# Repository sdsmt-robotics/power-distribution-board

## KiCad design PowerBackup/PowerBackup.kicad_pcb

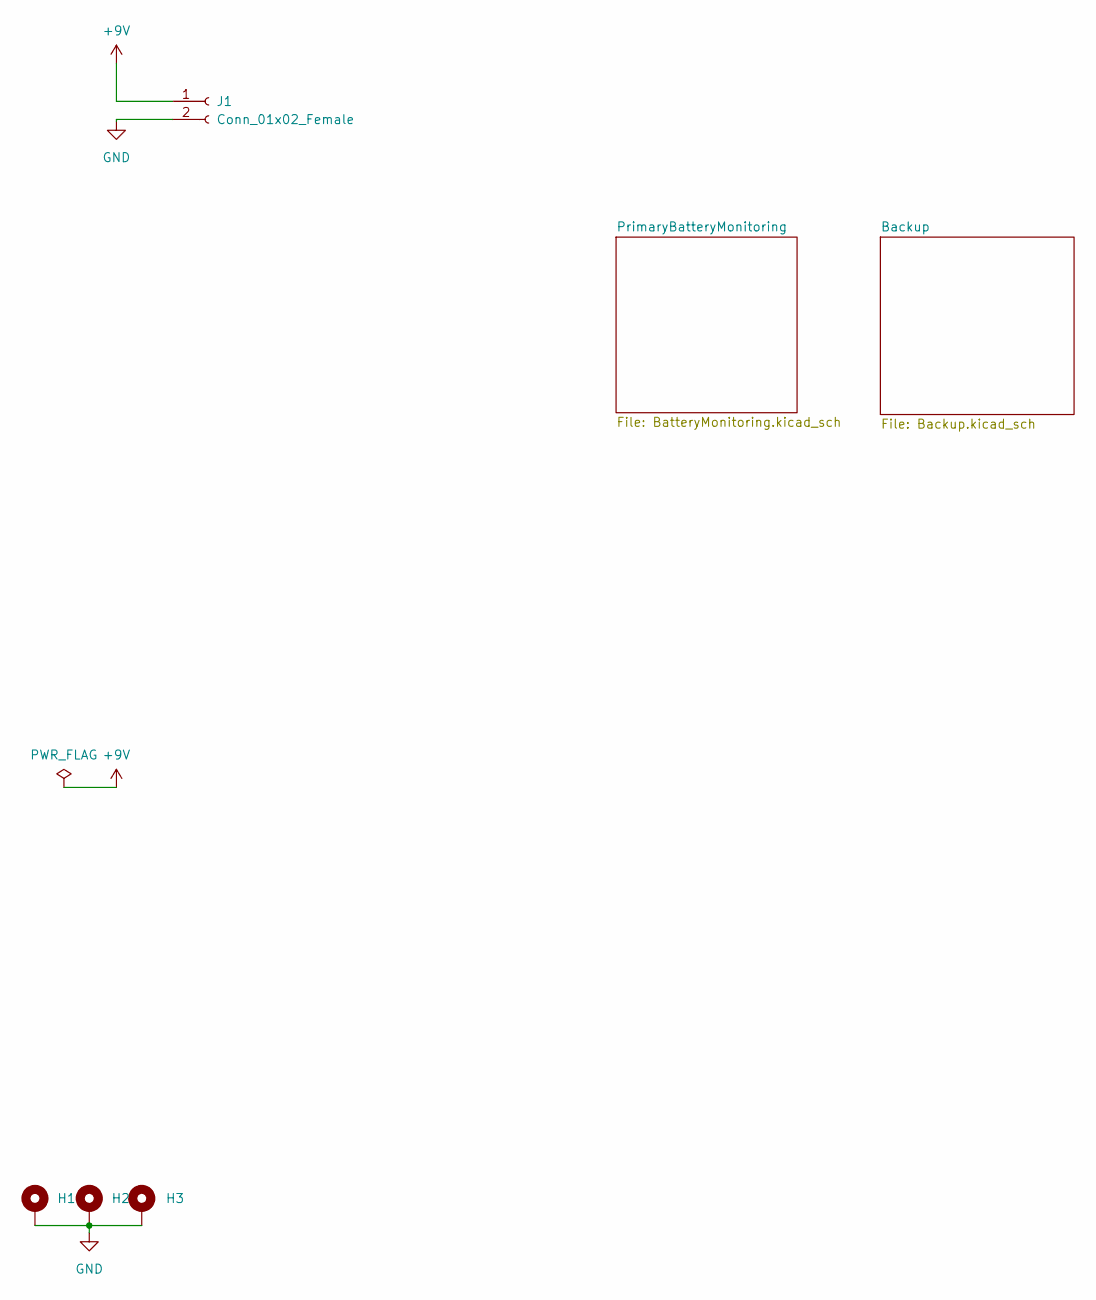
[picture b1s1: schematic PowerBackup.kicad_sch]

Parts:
H1, H2, H3: MountingHole_Pad; MountingHole_2.7mm_M2.5_Pad
J1: Conn_01x02_Female; JST_XH_B2B-XH-A_1x02_P2.50mm_Vertical

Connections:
+9V: J1.1; also elsewhere on the board
GND: H1.1, H2.1, H3.1, J1.2; also elsewhere on the board

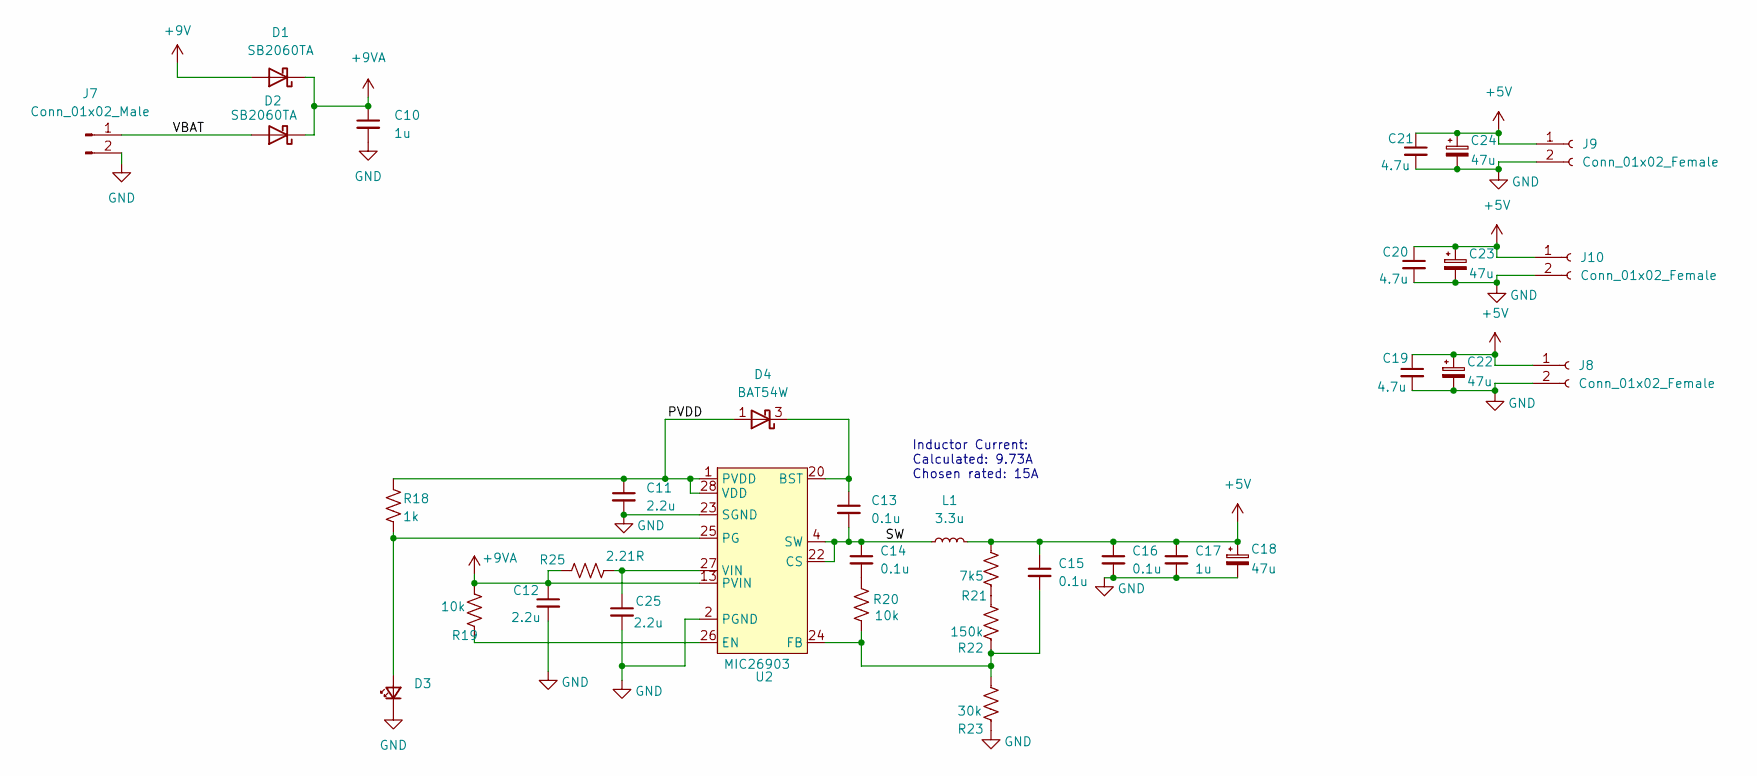
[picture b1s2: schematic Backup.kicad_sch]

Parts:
C10, C17: 1u; C_0603_1608Metric
C11, C12, C25: 2.2u; C_0603_1608Metric
C13, C14, C15, C16: 0.1u; C_0603_1608Metric
C18, C22, C23, C24: 47u; CP_EIA-6032-15_Kemet-U
C19, C20, C21: 4.7u; C_0603_1608Metric
D1, D2: SB2060TA; D_A-405_P5.08mm_Vertical_KathodeUp
D3: LED_Small; LED_0805_2012Metric
D4: BAT54W; SOT-323_SC-70
J7: Conn_01x02_Male; JST_XH_B2B-XH-A_1x02_P2.50mm_Vertical
J8, J9, J10: Conn_01x02_Female; JST_XH_B2B-XH-A_1x02_P2.50mm_Vertical
L1: 3.3u; Inductor_EXL1V0707-3R3-R
R18: 1k; R_0603_1608Metric
R19, R20: 10k; R_0603_1608Metric
R21: 7k5; R_0603_1608Metric
R22: 150k; R_0603_1608Metric
R23: 30k; R_0603_1608Metric
R25: 2.21R; R_0603_1608Metric
U2: MIC26903; MIC26903YJL-TR

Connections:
+5V: C15.1, C16.1, C17.1, C18.1, C19.1, C20.1, C21.1, C22.1, C23.1, C24.1, J8.1, J9.1, J10.1, L1.2, R21.1
+9V: D1.2 (A); also elsewhere on the board
+9VA: C10.1, C12.1, D1.1 (K), D2.1 (K), R19.1, R25.1, U2.13 (PVIN), U2.14 (PVIN), U2.15 (PVIN), U2.16 (PVIN), U2.17 (PVIN), U2.18 (PVIN), U2.19 (PVIN)
/Backup/PVDD: C11.1, D4.1 (A), R18.1, U2.1 (PVDD), U2.28 (VDD)
/Backup/SW: C13.2, C14.1, L1.1, U2.4 (SW), U2.9 (SW), U2.10 (SW), U2.11 (SW), U2.12 (SW), U2.22 (CS)
/Backup/VBAT: D2.2 (A), J7.1
GND: C10.2, C11.2, C12.2, C16.2, C17.2, C18.2, C19.2, C20.2, C21.2, C22.2, C23.2, C24.2, C25.2, D3.1 (K), J7.2, J8.2, J9.2, J10.2, R23.2, U2.2 (PGND), U2.5 (PGND), U2.6 (PGND), U2.7 (PGND), U2.8 (PGND), U2.21 (PGND), U2.23 (SGND); also elsewhere on the board
unnamed: C13.1, D4.3 (K), U2.20 (BST)
unnamed: C14.2, R20.1
unnamed: C15.2, R20.2, R22.2, R23.1, U2.24 (FB)
unnamed: C25.1, R25.2, U2.27 (VIN)
unnamed: D3.2 (A), R18.2, U2.25 (PG)
unnamed: R19.2, U2.26 (EN)
unnamed: R21.2, R22.1

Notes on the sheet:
Inductor Current: Calculated: 9.73A Chosen rated: 15A

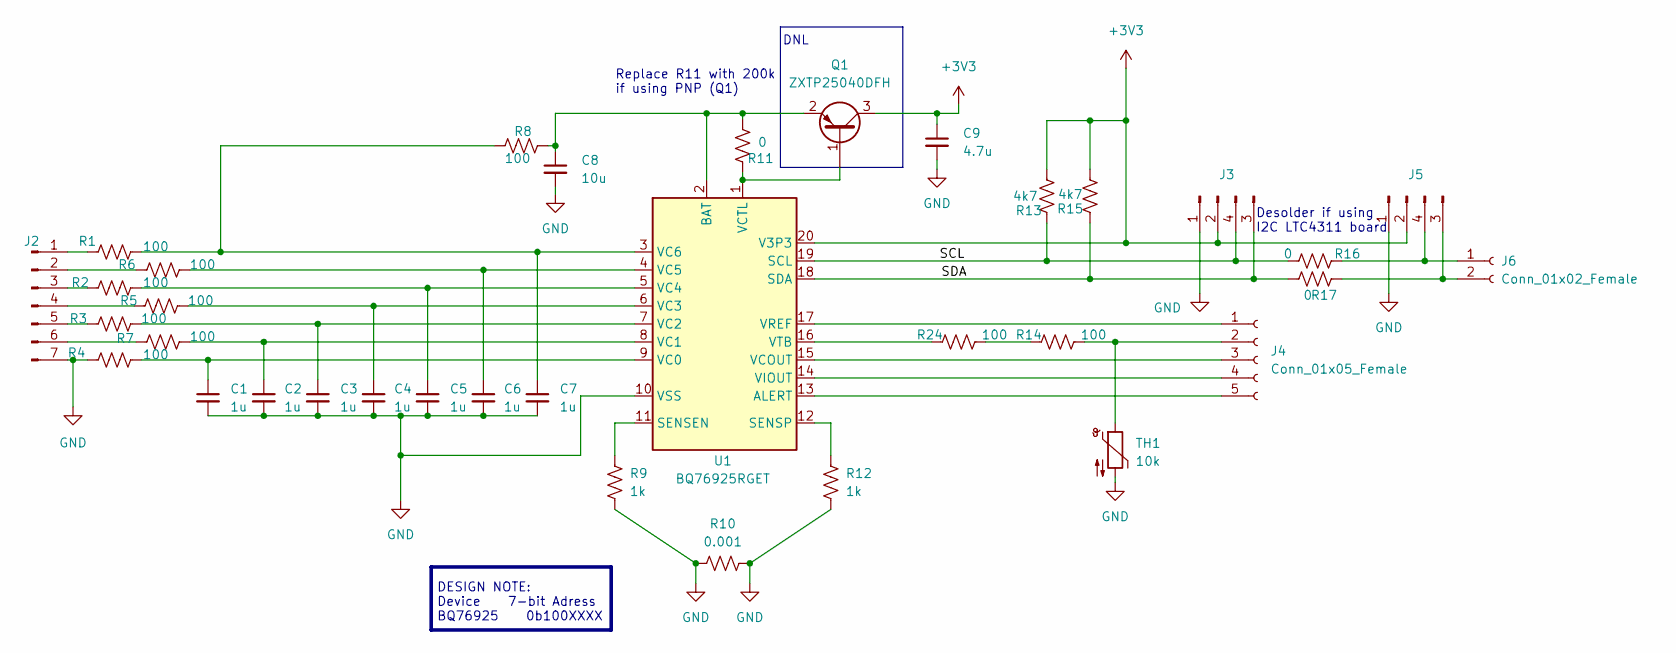
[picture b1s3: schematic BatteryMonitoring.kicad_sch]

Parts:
C1, C2, C3, C4, C5, C6, C7: 1u; C_0603_1608Metric
C8: 10u; C_0603_1608Metric
C9: 4.7u; C_0603_1608Metric
J2: Conn_01x07_Male; JST_XH_B7B-XH-A_1x07_P2.50mm_Vertical
J3, J5: Conn_01x04_Male; JST_SH_BM04B-SRSS-TB_1x04-1MP_P1.00mm_Vertical
J4: Conn_01x05_Female; PinHeader_1x05_P1.00mm_Vertical_SMD_Pin1Left
J6: Conn_01x02_Female; JST_XH_B2B-XH-A_1x02_P2.50mm_Vertical
Q1: ZXTP25040DFH; SOT-23
R1, R2, R3, R4, R5, R6, R7, R8, R14, R24: 100; R_0805_2012Metric
R9, R12: 1k; R_0603_1608Metric
R10: 0.001; R_0805_2012Metric
R11, R16, R17: 0; R_0805_2012Metric
R13, R15: 4k7; R_0805_2012Metric
TH1: 10k; R_0805_2012Metric
U1: BQ76925RGET; HVQFN-24-1EP_4x4mm_P0.5mm_EP2.5x2.5mm

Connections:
+3V3: C9.1, J3.2, J5.2, Q1.3 (C), R13.2, R15.2, U1.20 (V3P3)
/PrimaryBatteryMonitoring/SCL: J3.4 (Pin_3), R13.1, R16.2, U1.19 (SCL)
/PrimaryBatteryMonitoring/SDA: J3.3 (Pin_4), R15.1, R17.2, U1.18 (SDA)
GND: C1.2, C2.2, C3.2, C4.2, C5.2, C6.2, C7.2, C8.2, C9.2, J2.7, J3.1, J5.1, R4.1, R9.2, R10.1, R10.2, R12.2, TH1.2, U1.10 (VSS); also elsewhere on the board
unnamed: C1.1, R4.2, U1.9 (VC0)
unnamed: C2.1, R7.2, U1.8 (VC1)
unnamed: C3.1, R3.2, U1.7 (VC2)
unnamed: C4.1, R5.2, U1.6 (VC3)
unnamed: C5.1, R2.2, U1.5 (VC4)
unnamed: C6.1, R6.2, U1.4 (VC5)
unnamed: C7.1, R1.2, R8.1, U1.3 (VC6)
unnamed: C8.1, Q1.2 (E), R8.2, R11.2, U1.2 (BAT)
unnamed: J2.1, R1.1
unnamed: J2.2, R6.1
unnamed: J2.3, R2.1
unnamed: J2.4, R5.1
unnamed: J2.5, R3.1
unnamed: J2.6, R7.1
unnamed: J4.1, U1.17 (VREF)
unnamed: J4.2, R14.2, TH1.1
unnamed: J4.3, U1.15 (VCOUT)
unnamed: J4.4, U1.14 (VIOUT)
unnamed: J4.5, U1.13 (ALERT)
unnamed: J5.3 (Pin_4), J6.2, R17.1
unnamed: J5.4 (Pin_3), J6.1, R16.1
unnamed: Q1.1 (B), R11.1, U1.1 (VCTL)
unnamed: R9.1, U1.11 (SENSEN)
unnamed: R12.1, U1.12 (SENSP)
unnamed: R14.1, R24.2
unnamed: R24.1, U1.16 (VTB)

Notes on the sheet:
Desolder if using I2C LTC4311 board
DNL
Replace R11 with 200k if using PNP (Q1)
DESIGN NOTE: Device 7-bit Adress BQ76925 0b100XXXX

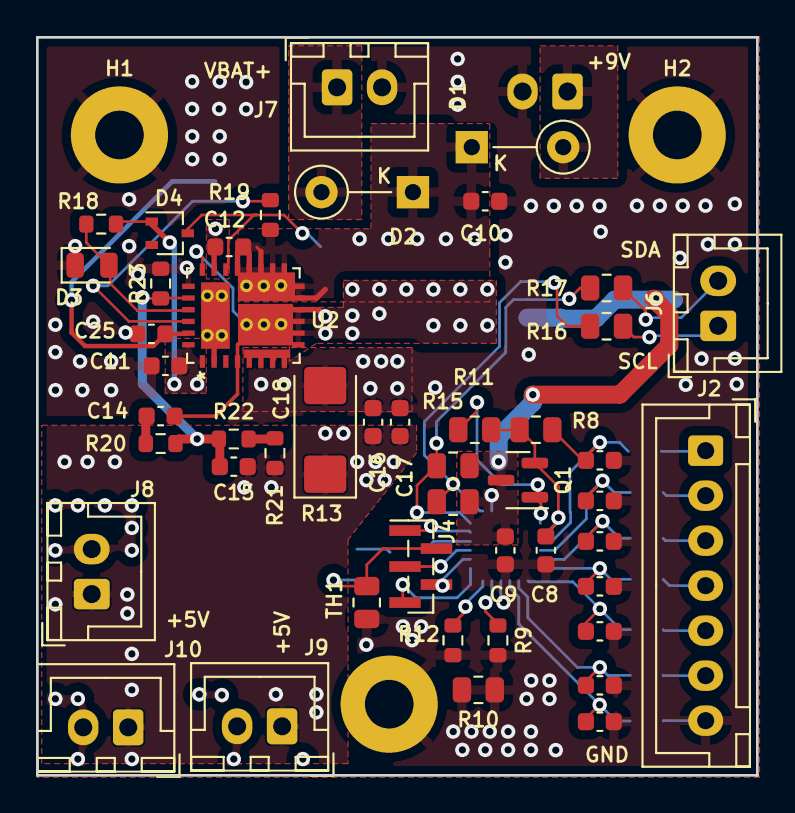
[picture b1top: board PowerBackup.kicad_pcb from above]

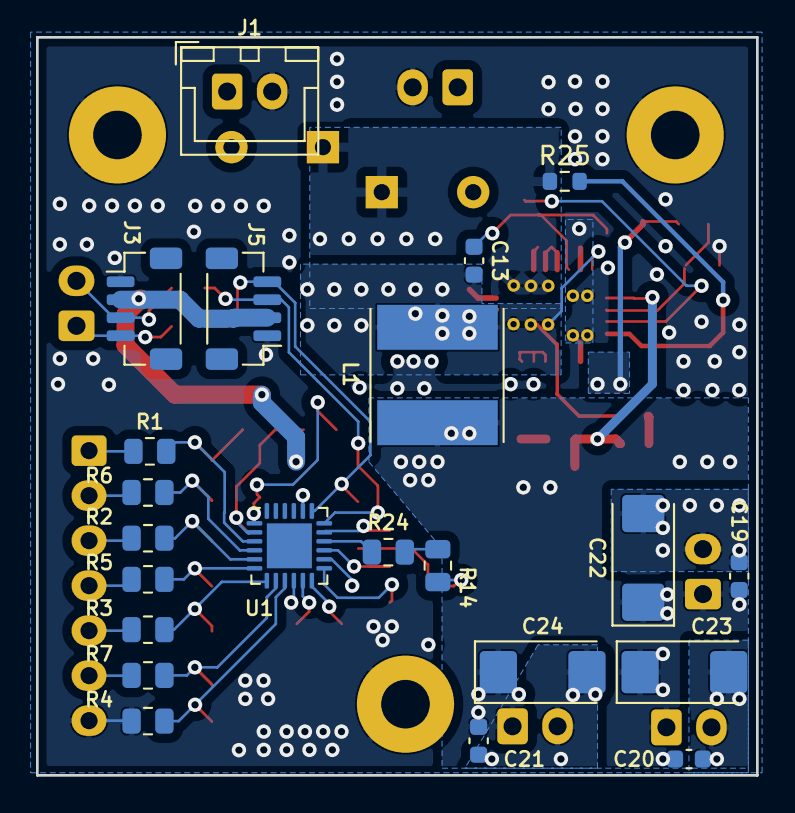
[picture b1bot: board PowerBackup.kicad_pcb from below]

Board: 4 copper layers, 40.0 x 41.0 mm, 72 parts (22 on the bottom side), 43 nets.

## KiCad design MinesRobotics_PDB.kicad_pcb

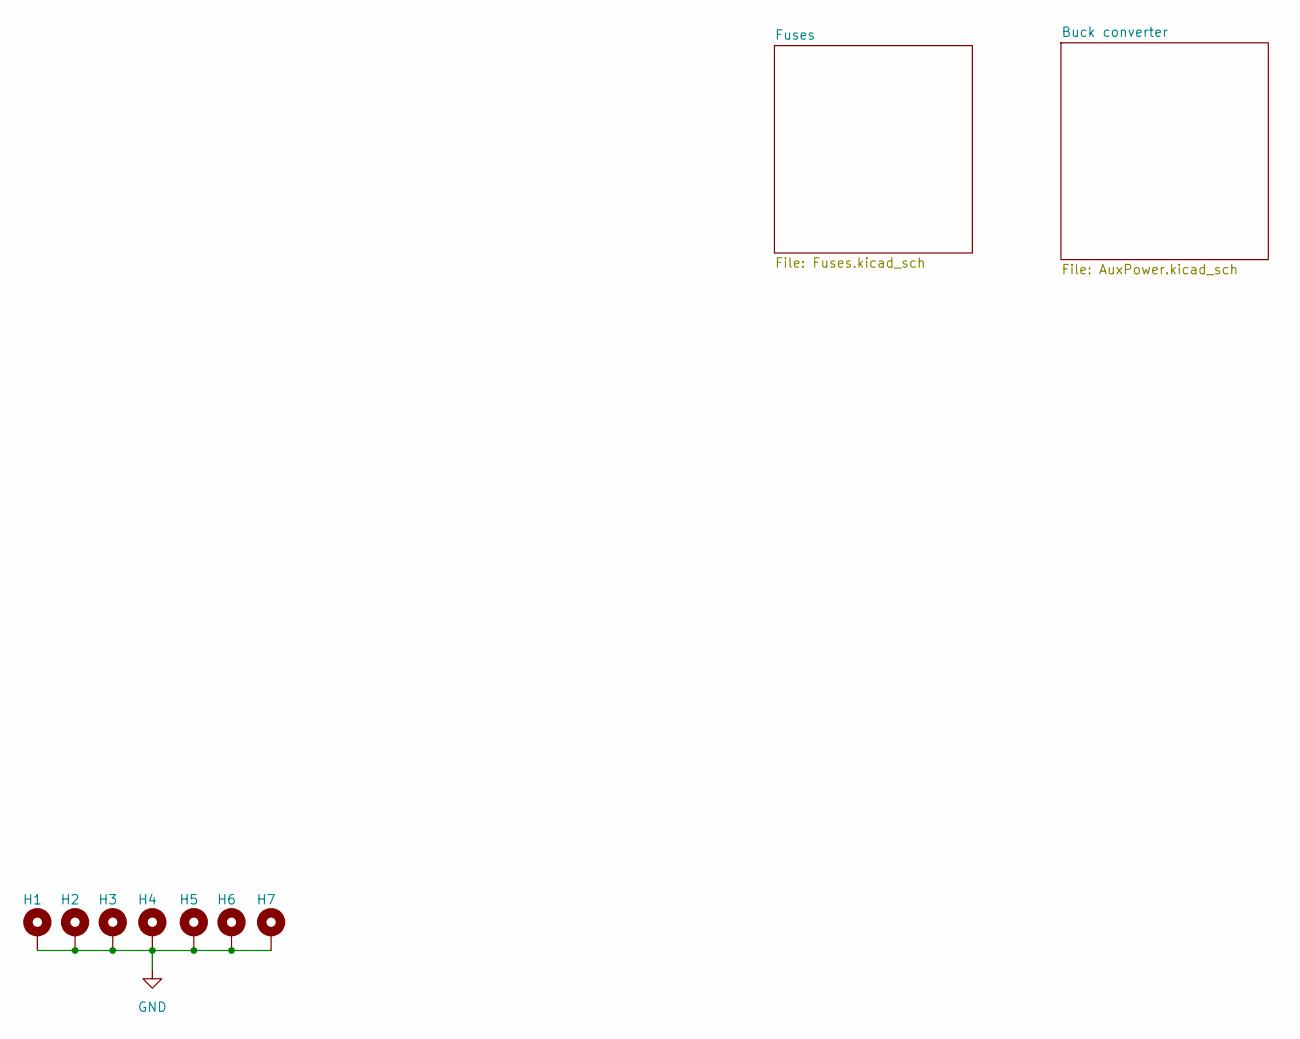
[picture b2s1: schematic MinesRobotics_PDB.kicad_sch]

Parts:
H1, H2, H3, H4, H5, H6, H7: MountingHole_Pad; MountingHole_3.2mm_M3_DIN965_Pad

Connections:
GND: H1.1, H2.1, H3.1, H4.1, H5.1, H6.1, H7.1; also elsewhere on the board

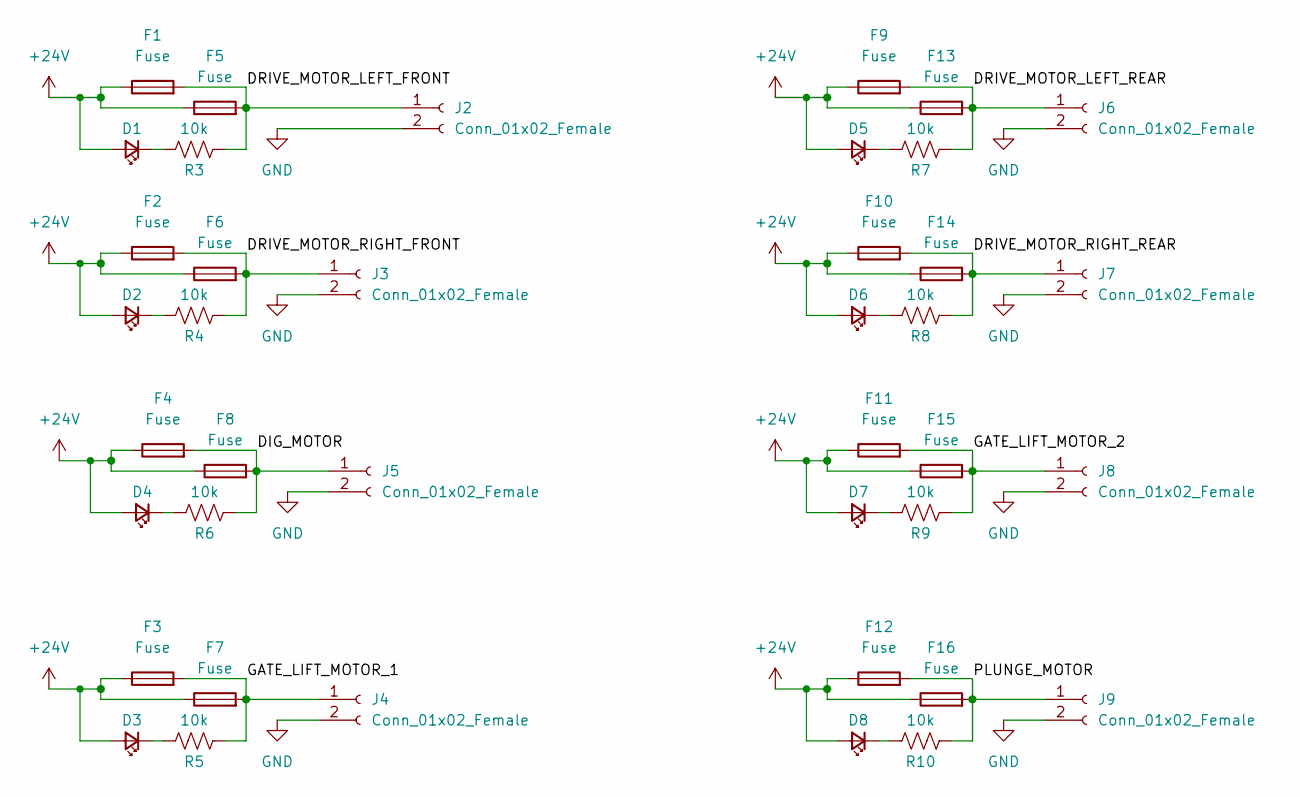
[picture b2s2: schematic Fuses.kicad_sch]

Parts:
D1, D2, D3, D4, D5, D6, D7, D8: LED_Small; LED_0603_1608Metric
F1, F2, F3, F4, F5, F6, F7, F8, F9, F10, F11, F12, F13, F14, F15, F16: Fuse; Fuseholder_Blade_Mini_Keystone_3568
J2, J3, J4, J5, J6, J7, J8, J9: Conn_01x02_Female; PowerPole_45A_Vert
R3, R4, R5, R6, R7, R8, R9, R10: 10k; R_0603_1608Metric

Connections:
+24V: D1.2 (A), D2.2 (A), D3.2 (A), D4.2 (A), D5.2 (A), D6.2 (A), D7.2 (A), D8.2 (A), F1.1, F2.1, F3.1, F4.1, F5.1, F6.1, F7.1, F8.1, F9.1, F10.1, F11.1, F12.1, F13.1, F14.1, F15.1, F16.1; also elsewhere on the board
/Fuses/DIG_MOTOR: F4.2, F8.2, J5.1, R6.2
/Fuses/DRIVE_MOTOR_LEFT_FRONT: F1.2, F5.2, J2.1, R3.2
/Fuses/DRIVE_MOTOR_LEFT_REAR: F9.2, F13.2, J6.1, R7.2
/Fuses/DRIVE_MOTOR_RIGHT_FRONT: F2.2, F6.2, J3.1, R4.2
/Fuses/DRIVE_MOTOR_RIGHT_REAR: F10.2, F14.2, J7.1, R8.2
/Fuses/GATE_LIFT_MOTOR_1: F3.2, F7.2, J4.1, R5.2
/Fuses/GATE_LIFT_MOTOR_2: F11.2, F15.2, J8.1, R9.2
/Fuses/PLUNGE_MOTOR: F12.2, F16.2, J9.1, R10.2
GND: J2.2, J3.2, J4.2, J5.2, J6.2, J7.2, J8.2, J9.2; also elsewhere on the board
unnamed: D1.1 (K), R3.1
unnamed: D2.1 (K), R4.1
unnamed: D3.1 (K), R5.1
unnamed: D4.1 (K), R6.1
unnamed: D5.1 (K), R7.1
unnamed: D6.1 (K), R8.1
unnamed: D7.1 (K), R9.1
unnamed: D8.1 (K), R10.1

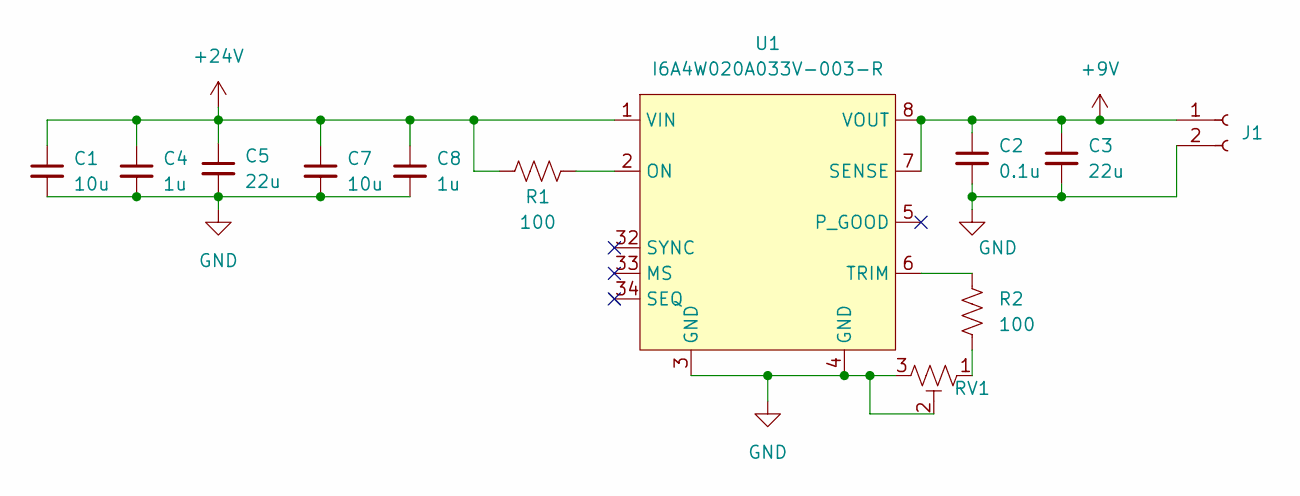
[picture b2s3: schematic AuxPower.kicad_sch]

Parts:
C1, C7: 10u; C_0603_1608Metric
C2: 0.1u; C_0603_1608Metric
C3, C5: 22u; CP_EIA-7343-15_Kemet-W
C4, C8: 1u; C_0603_1608Metric
J1: Conn_01x02_Female; JST_XH_B2B-XH-A_1x02_P2.50mm_Vertical
R1, R2: 100; R_0805_2012Metric
RV1: 50k; Potentiometer_Bourns_3266Y_Vertical
U1: I6A4W020A033V-003-R; i6A4W

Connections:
+9V: C2.1, C3.1, J1.1, U1.7 (SENSE), U1.8 (VOUT)
+24V: C1.1, C4.1, C5.1, C7.1, C8.1, R1.1, U1.1 (VIN), U1.33 (MS); also elsewhere on the board
GND: C1.2, C2.2, C3.2, C4.2, C5.2, C7.2, C8.2, J1.2, RV1.2, RV1.3, U1.3 (GND), U1.4 (GND); also elsewhere on the board
unnamed 19: R1.2, U1.2 (ON); also elsewhere on the board
unnamed: R2.1, U1.6 (TRIM)
unnamed: R2.2, RV1.1
unnamed 22: U1.34 (SEQ); also elsewhere on the board

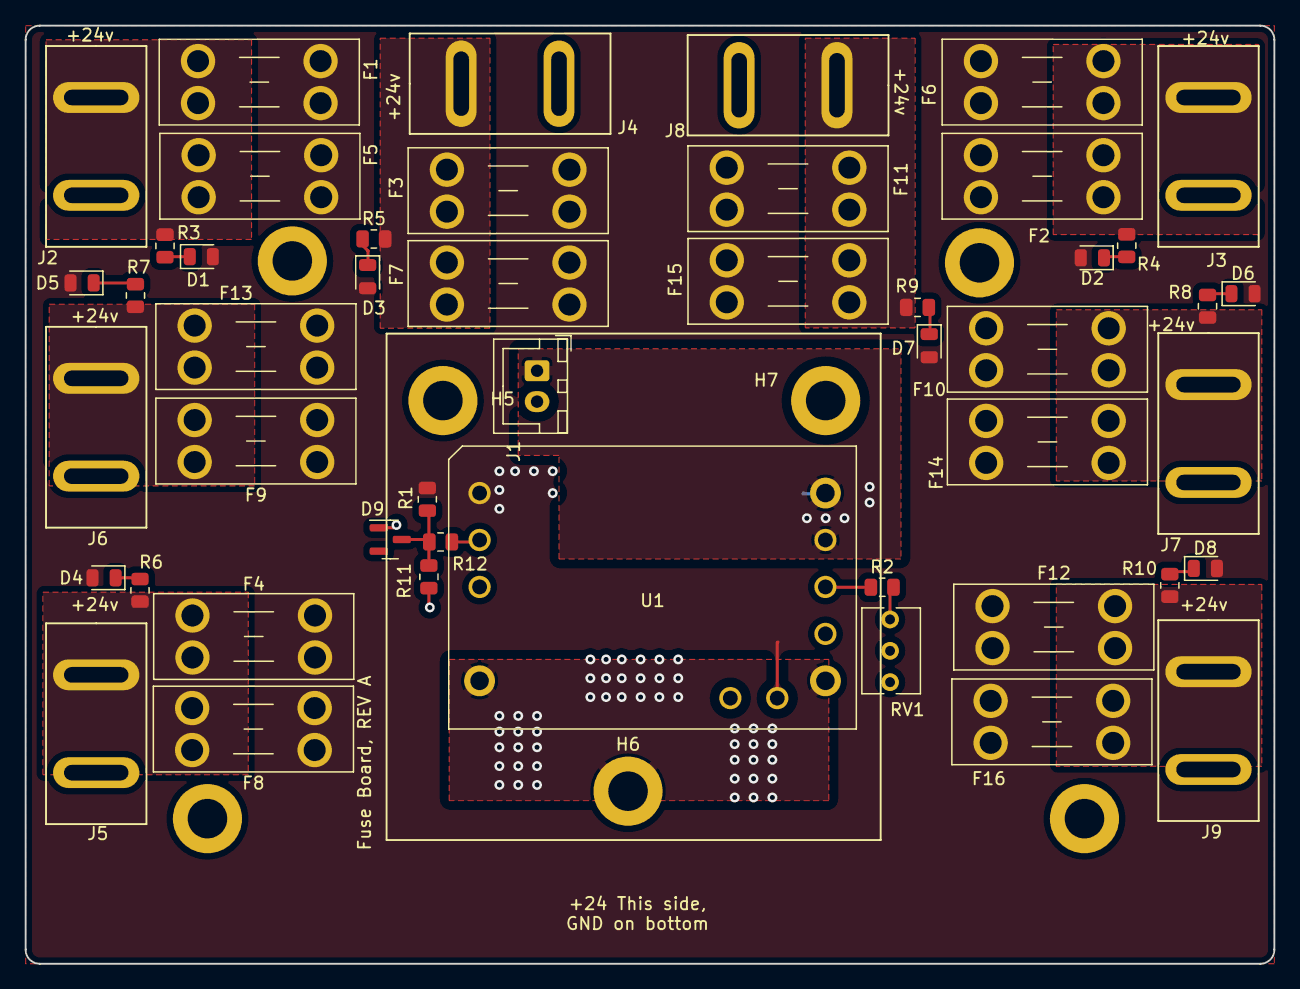
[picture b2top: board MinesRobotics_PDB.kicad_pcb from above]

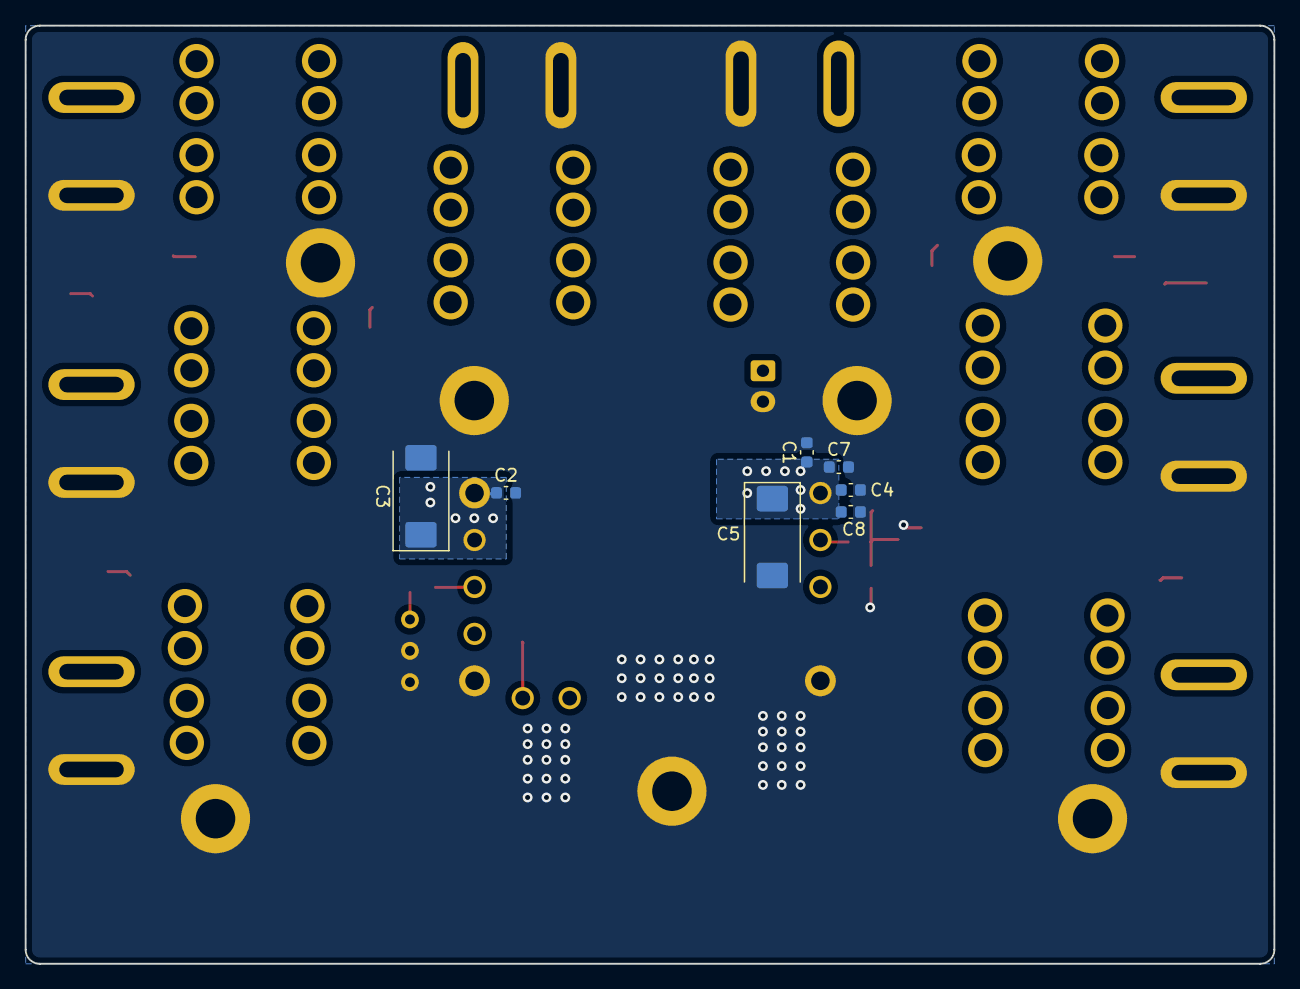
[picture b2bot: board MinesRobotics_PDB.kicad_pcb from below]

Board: 2 copper layers, 101.1 x 75.9 mm, 62 parts (7 on the bottom side), 23 nets.

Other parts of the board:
D9: BZX8450-C2V2VL; SOT-23
R11: 150; R_0805_2012Metric
R12: 10k; R_0805_2012Metric

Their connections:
GND: D9.1 (A), R11.2; also elsewhere on the board
unnamed 19: D9.3 (K), R11.1, R12.1; also elsewhere on the board
unnamed 22: R12.2; also elsewhere on the board

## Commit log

2022-02-04 Adding old kicad files
2022-02-12 Updated according to requirements
2022-02-13 Added 9V buck converter
2022-02-13 Cleaning up for prototype run
2022-02-13 Still cleaning up
2022-02-13 Added schematic and PCB pdf's
2022-02-14 No point using Fuses w/o fuse holders, Also added 3D models
2022-02-14 Updating gitignore file
2022-02-14 Added BOM and updated Cap footprint according to availability
2022-02-16 starting Backup board and updated 3D model
2022-02-17 Changed resistors and LEDs to 0805 and updated Production files
2022-02-17 Did some initial board layout
2022-02-17 Trying things
2022-02-19 Adding regulator
2022-02-19 Moved daughter board up a tiny bit
2022-02-20 Added 5V 9A buck converter
2022-02-20 Looking over desing
2022-02-21 Added Qwiic connector
2022-02-21 fixed 9V regulator circuit
2022-02-21 Adding production files for power backup
2022-03-01 Added BOM and production files
2022-03-13 Pvin is connected to Vin through a 2.21R resistor
2022-03-15 Updating production files
2022-03-16 Commiting before order, Regenerated gerbers for both boards
